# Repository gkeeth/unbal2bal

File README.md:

# Unbalanced to Balanced Audio Converter

Intended for measurements of unbalanced sources with a balanced soundcard.

Powered from +/-12V DC on a 3-pin Mini DIN connector.
Outputs (unbuffered) +/-12V DC on a 4-pin Mini DIN connector, to allow daisy chaining.

## License
This work is licensed under a [Creative Commons Attribution-ShareAlike 4.0
International License][cc-by-sa].

[![CC BY-SA 4.0][cc-by-sa-image]][cc-by-sa]

[cc-by-sa]: http://creativecommons.org/licenses/by-sa/4.0/
[cc-by-sa-image]: https://licensebuttons.net/l/by-sa/4.0/88x31.png
[cc-by-sa-shield]: https://img.shields.io/badge/License-CC%20BY--SA%204.0-lightgrey.svg

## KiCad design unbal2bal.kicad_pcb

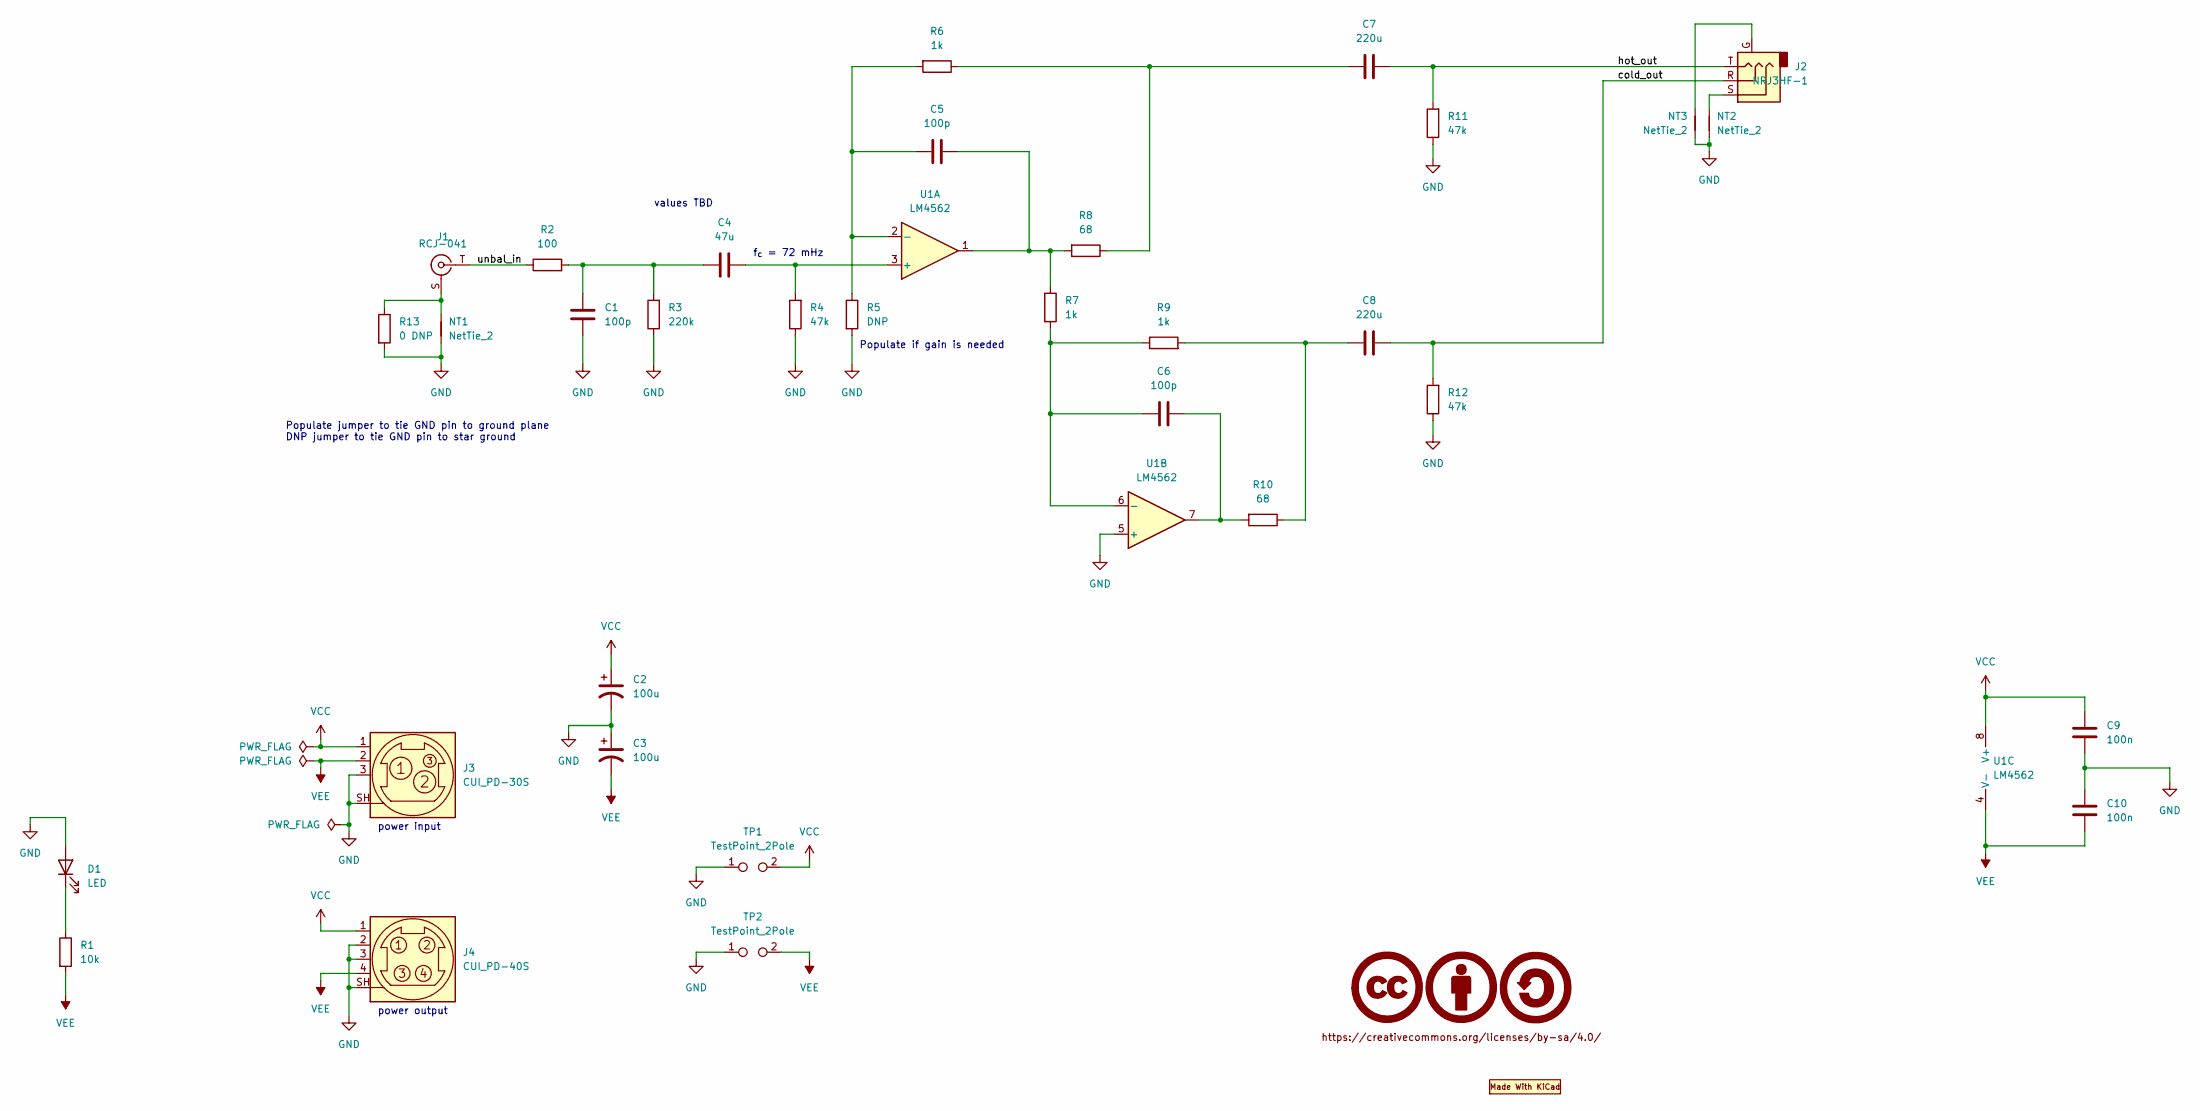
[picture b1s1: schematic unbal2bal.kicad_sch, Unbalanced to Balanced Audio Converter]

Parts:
C1, C5, C6: 100p; C_0805_2012Metric
C2, C3: 100u; CP_Radial_D6.3mm_P2.50mm; Voltage Rating 35V; Manufacturer PN UVR1V101MED
C4: 47u; C_Radial_D10.0mm_H16.0mm_P5.00mm; Voltage Rating 35V; Manufacturer PN UES1V470MPM
C7, C8: 220u; C_Radial_D12.5mm_H20.0mm_P5.00mm_Horizontal; Voltage Rating 35V; Manufacturer PN UVP1V221MHD
C9, C10: 100n; C_0805_2012Metric
D1: LED; LED_D5.0mm_Horizontal_O3.81mm_Z3.0mm
J1: RCJ-041; RCA_CUI_RCJ-04x_Horizontal; Manufacturer PN RCJ-041
J2: NRJ3HF-1; Jack_6.35mm_Neutrik_NRJ3HF-1_Horizontal; Manufacturer PN NRJ3HF-1
J3: CUI_PD-30S; Power-DIN_CUI_PD-30S_Horizontal; Manufacturer PN PD-30S
J4: CUI_PD-40S; Power-DIN_CUI_PD-40S_Horizontal; Manufacturer PN PD-40S
LOGO1: Logo_MadeWithKiCad; KiCad-Logo2_5mm_SilkScreen
LOGO2: CC-BY-SA_0.5in; CC-BY-SA_SilkScreenTop_Small
NT1, NT2: NetTie_2; NetTie-2_SMD_Pad1.0mm
NT3: NetTie_2; NetTie-2_SMD_Pad0.5mm
R1: 10k; R_1206_3216Metric
R2: 100; R_1206_3216Metric
R3: 220k; R_1206_3216Metric
R4, R11, R12: 47k; R_1206_3216Metric
R5: DNP; R_1206_3216Metric
R6, R7, R9: 1k; R_1206_3216Metric
R8, R10: 68; R_1206_3216Metric
R13: 0 DNP; R_1206_3216Metric
TP1, TP2: TestPoint_2Pole; PinHeader_1x02_P2.54mm_Vertical
U1: LM4562; SOIC-8_3.9x4.9mm_P1.27mm

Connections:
/cold_out: C8.2, J2.R, R12.2
/hot_out: C7.2, J2.T, R11.2
/unbal_in: J1.T, R2.1
GND: C1.2, C2.2, C3.1, C9.2, C10.1, D1.2 (A), J3.3, J3.SH (Shield), J4.2, J4.3, J4.SH (Shield), NT1.1, NT2.2, NT3.2, R3.1, R4.1, R5.2, R11.1, R12.1, R13.2, TP1.1, TP2.1, U1.5 (+)
unnamed: C1.1, C4.1, R2.2, R3.2
unnamed: C4.2, R4.2, U1.3 (+)
unnamed: C5.1, R5.1, R6.2, U1.2 (-)
unnamed: C5.2, R7.1, R8.2, U1.1
unnamed: C6.1, R7.2, R9.1, U1.6 (-)
unnamed: C6.2, R10.2, U1.7
unnamed: C7.1, R6.1, R8.1
unnamed: C8.1, R9.2, R10.1
unnamed: D1.1 (K), R1.1
unnamed: J1.S, NT1.2, R13.1
unnamed: J2.G, NT3.1
unnamed: J2.S, NT2.1
VCC: C2.1, C9.1, J3.1, J4.1, TP1.2, U1.8 (V+)
VEE: C3.2, C10.2, J3.2, J4.4 (Shield), R1.2, TP2.2, U1.4 (V-)

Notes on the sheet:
power output
values TBD
f_{c} = 72 mHz
Populate jumper to tie GND pin to ground plane DNP jumper to tie GND pin to star ground
power input
Populate if gain is needed

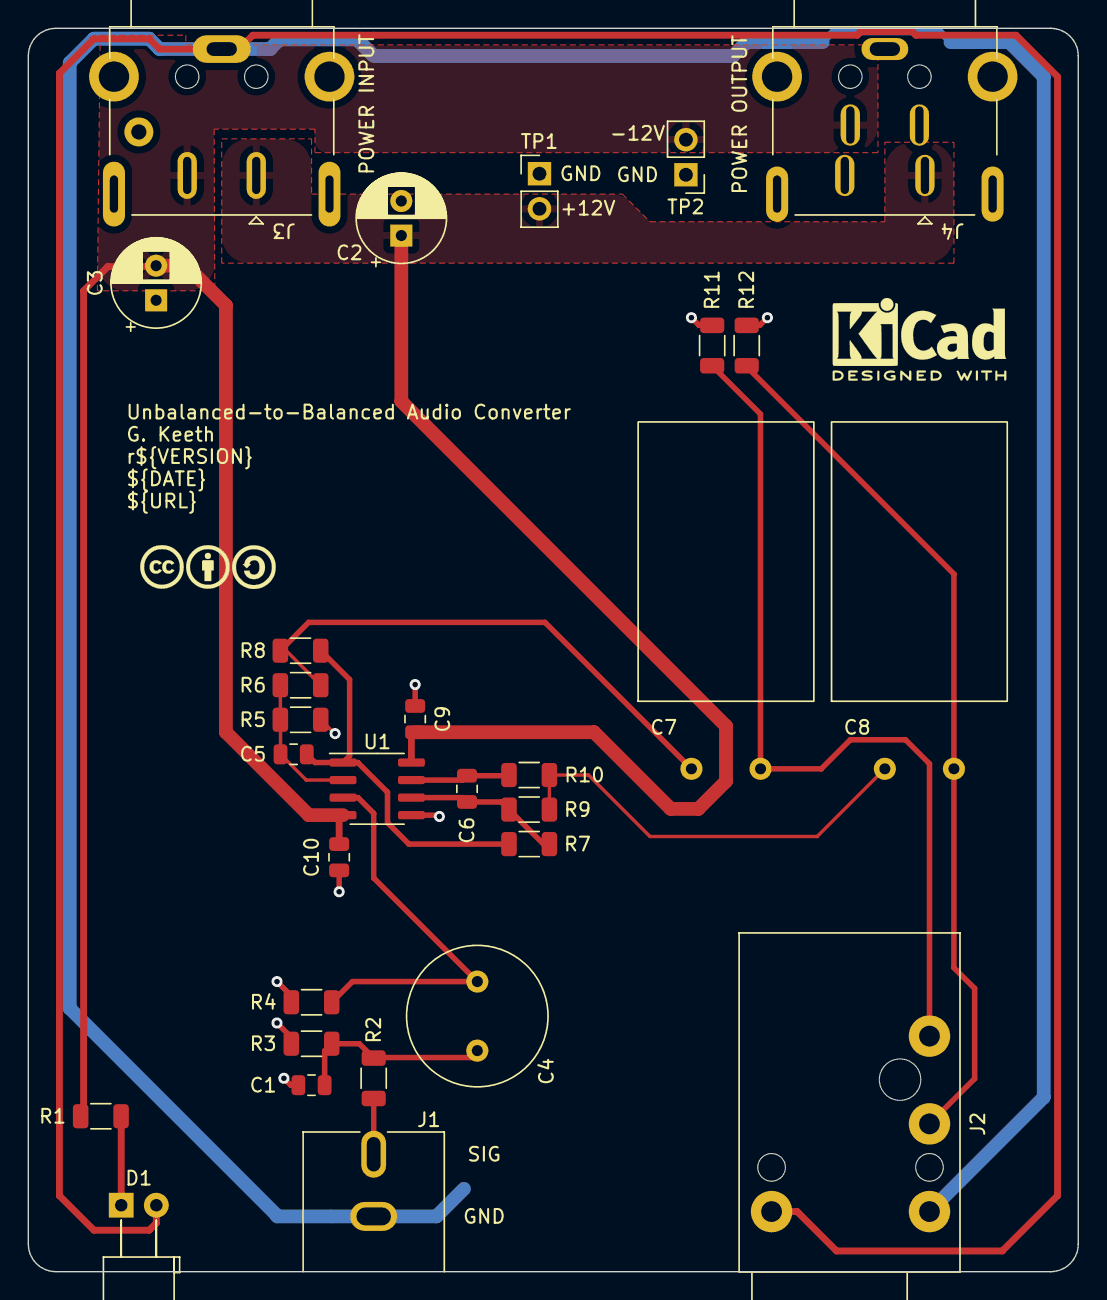
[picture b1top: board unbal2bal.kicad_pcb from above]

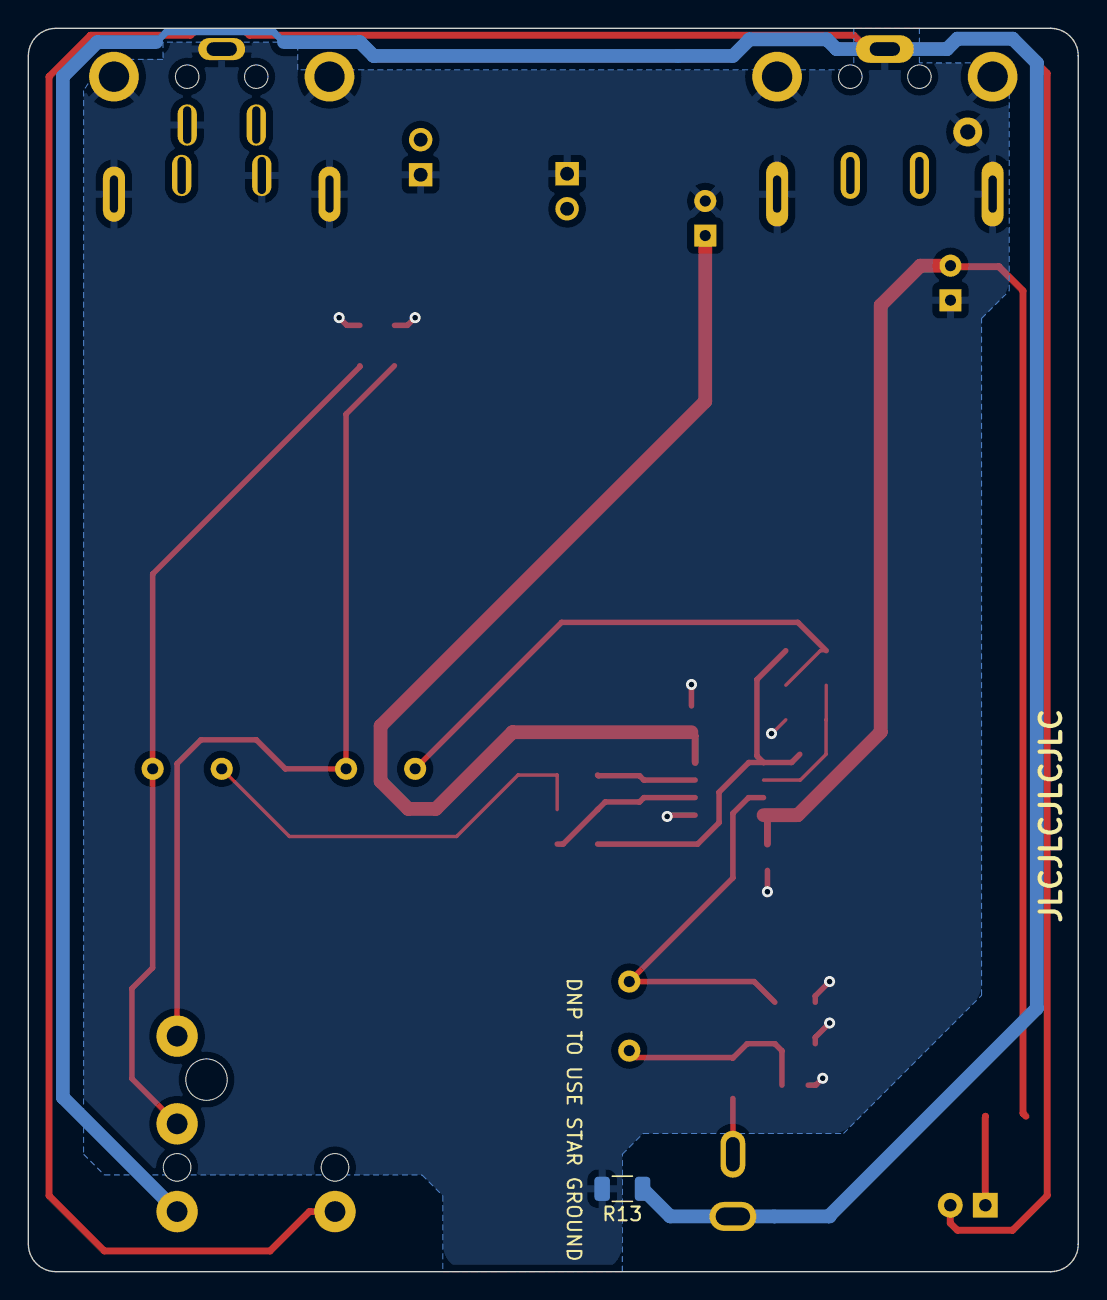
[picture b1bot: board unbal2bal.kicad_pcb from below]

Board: 2 copper layers, 76.0 x 90.0 mm, 36 parts (3 on the bottom side), 18 nets.

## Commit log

2022-06-11 mostly complete layout
2022-06-11 update TODO
2022-06-11 update gitignore
2022-06-11 remove renamed project files
2022-06-11 add license info to README
2022-06-12 add text version of license
2022-06-12 switch RCA jack to a nicer model
2022-06-12 update TODOs
2022-06-12 move output coupling caps to horizontal to fit into enclosure
2022-06-16 add SVG source files for mini-din label footprints
2022-06-16 add back panel pcb
2022-06-16 minor updates, labels, etc
2022-06-16 mechanical holes in front panel. needs labels
2022-06-18 update grounding
2022-06-18 add input/output label SVGs
2022-06-18 add front panel
2022-06-18 minor change from plotting gerbers
2022-06-18 update part numbers
2022-07-05 fix vertical position of RCA jack cutout
2022-07-05 change to lower profile 1/4in jack
2022-07-06 update front panel cutout for 1/4in jack
2022-08-28 Adjust DIN connector locations
    - move miniDIN (power) connectors backwards 1.6mm to be flush with
    outside of case for connector clearance
    - not going to increase size of cutouts for miniDIN connectors in back
    panel. Moving the connectors fixes the connector clearance issue, and
    existing cutouts have a minimal amount of slop so hopefully that
    should be enough for assembly tolerances.
2022-08-28 add mask cutout for balanced jack panel grounding
2022-08-28 add 3D model for output jack, update date
2022-08-28 update front panel date on silk
2022-09-06 increase annular ring size on rca connector, bump to r2
2022-09-06 add ibom
2022-09-08 Add logo graphic
2022-09-08 update ibom
2022-09-08 add logo to front panel (r3)
2022-09-08 add labels for frontpanel
2022-09-08 add mechanical files
2022-10-08 add power DIN source svgs
2022-10-08 swap to power DIN connectors for back panel
2022-10-08 switch to power DIN connectors on main board
2022-10-08 adjust text position on power-din labels
2022-10-08 swap to round cutouts for power-din connectors
2022-10-08 complete TODOs (and fix rev#)

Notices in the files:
unbal2bal.kicad_sch:
https://creativecommons.org/licenses/by-sa/4.0
